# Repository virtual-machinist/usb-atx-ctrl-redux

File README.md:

# usb-atx-ctrl-redux

## Rationale

This project is a minified/reduced version of [usb-atx-ctrl](https://github.com/zappanaut/usb-atx-ctrl) project by Zappanaut.

The rationale behind this project is to have a standard PiKVM ATX breakout board installed in the case of the PC being controlled vs replacing it with a custom PCB like done in the aforementioned project.

## Design Choices and Components Used

1. RP2040-Zero (`RZ1`) is not soldered to the PCB directly, but using SMD female pin headers. If needed `RZ1` can be soldered through a set of male pin headers. This might however require offsetting the USB-C socket in the case model.  
2. `SW1` and `SW2` are 4.5x4.5x5mm 90° through-hole miniature tactile push-button switches with distance between the shield and switch terminals is ~2.0mm.

## Assembly

Assembly starts with SMD components, typically resistors, then LEDs, then optorelays. After that RP2040-Zero, tactile switches, then 8P8C socket.  

After PCB assembly it's recommended to print and use a [case](case/README.md) to protect the PCB from accidental damage and electrical shorts.

Assembled photos can be seen under [pictures](pictures/README.md).

## Usage

Setting up the RP2040-Zero is the same as in [usb-atx-ctrl](https://github.com/zappanaut/usb-atx-ctrl) project. The project requires a PC with an [ATX breakout board](https://github.com/pikvm/pikvm/blob/master/docs/atx_board.md) from the PiKVM project or some other solution that exposes a [compatible](https://github.com/pikvm/pikvm/blob/master/docs/atx_board/rj45.jpg) RJ-45 connector. 

## License

The project uses MIT license, except for the case which is [licensed](case/LICENSE) under Creative Commons Attribution 4.0 license ("CC-BY").

## Credits

1. [usb-atx-ctrl](https://github.com/zappanaut/usb-atx-ctrl) project by Zappanaut for most of the schematics and some of the symbols.

2. [Wright-Train-Works](https://github.com/acwright/Wright-Train-Works) project by Aaron Wright for the Amphenol connector STEP file.

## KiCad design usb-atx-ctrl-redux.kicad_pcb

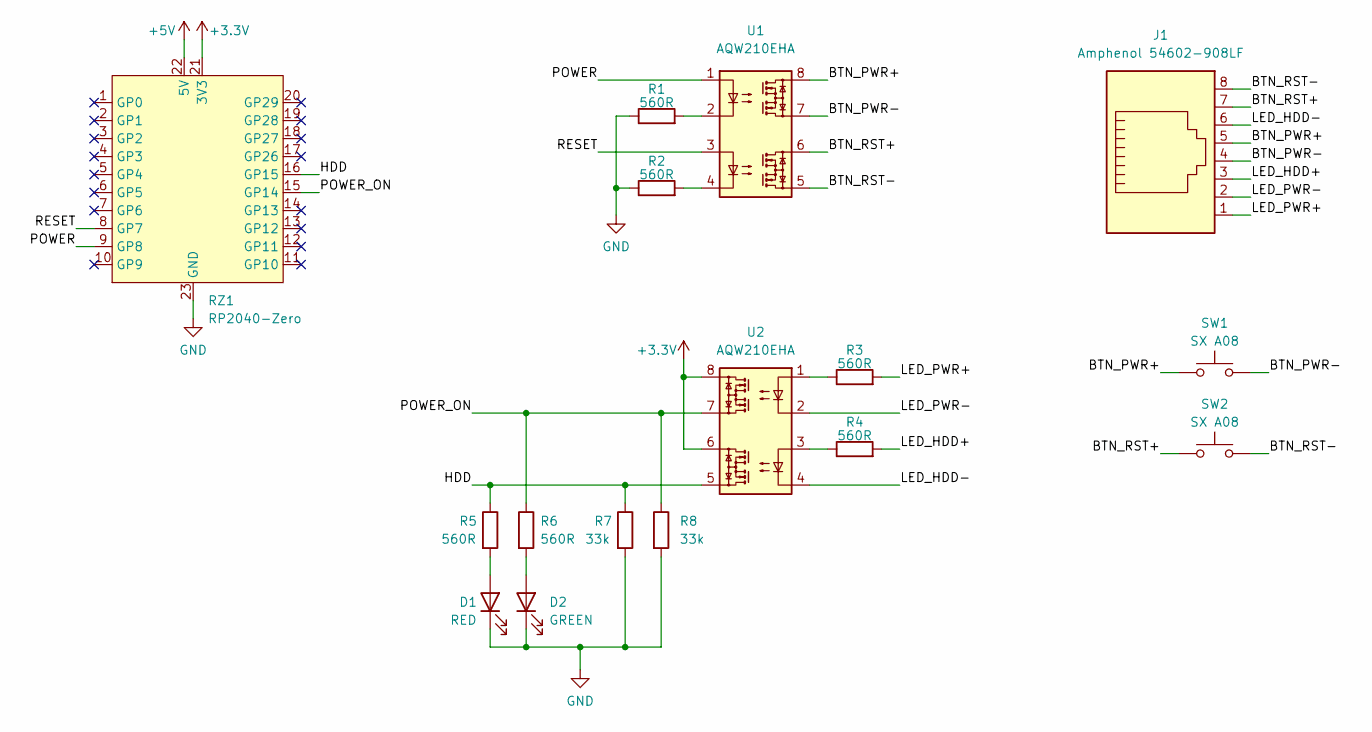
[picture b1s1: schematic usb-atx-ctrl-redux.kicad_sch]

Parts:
D1: RED; LED_0805_2012Metric_Pad1.15x1.40mm_HandSolder
D2: GREEN; LED_0805_2012Metric_Pad1.15x1.40mm_HandSolder
J1: Amphenol 54602-908LF; RJ45_Amphenol_54602-x08_Horizontal
R1, R2, R3, R4, R5, R6: 560R; R_0603_1608Metric_Pad0.98x0.95mm_HandSolder
R7, R8: 33k; R_0603_1608Metric_Pad0.98x0.95mm_HandSolder
RZ1: RP2040-Zero; RP2040-Zero_SMD
SW1, SW2: SX A08; Button_Switch_SX_A08
U1, U2: AQW210EHA; SMDIP-8_W7.62mm

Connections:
+3.3V: RZ1.21 (3V3), U2.6, U2.8
+5V: RZ1.22 (5V)
/BTN_PWR+: J1.5, SW1.1, U1.8
/BTN_PWR-: J1.4, SW1.2, U1.7
/BTN_RST+: J1.7, SW2.1, U1.6
/BTN_RST-: J1.8, SW2.2, U1.5
/HDD: R5.1, R7.1, RZ1.16 (GP15), U2.5
/LED_HDD+: J1.3, R4.2
/LED_HDD-: J1.6, U2.4
/LED_PWR+: J1.1, R3.2
/LED_PWR-: J1.2, U2.2
/POWER: RZ1.9 (GP8), U1.1
/POWER_ON: R6.1, R8.1, RZ1.15 (GP14), U2.7
/RESET: RZ1.8 (GP7), U1.3
GND: D1.1 (K), D2.1 (K), R1.1, R2.1, R7.2, R8.2, RZ1.23 (GND)
unnamed: D1.2 (A), R5.2
unnamed: D2.2 (A), R6.2
unnamed: R1.2, U1.2
unnamed: R2.2, U1.4
unnamed: R3.1, U2.1
unnamed: R4.1, U2.3

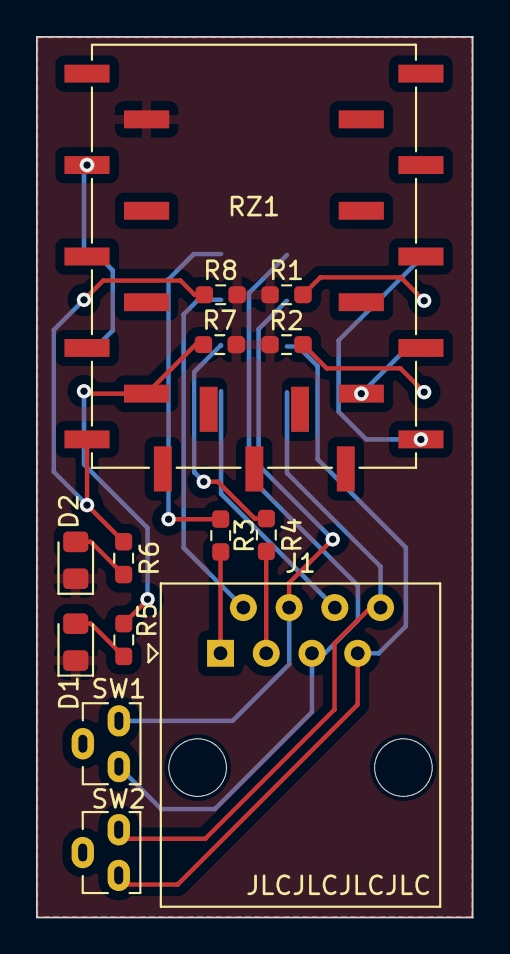
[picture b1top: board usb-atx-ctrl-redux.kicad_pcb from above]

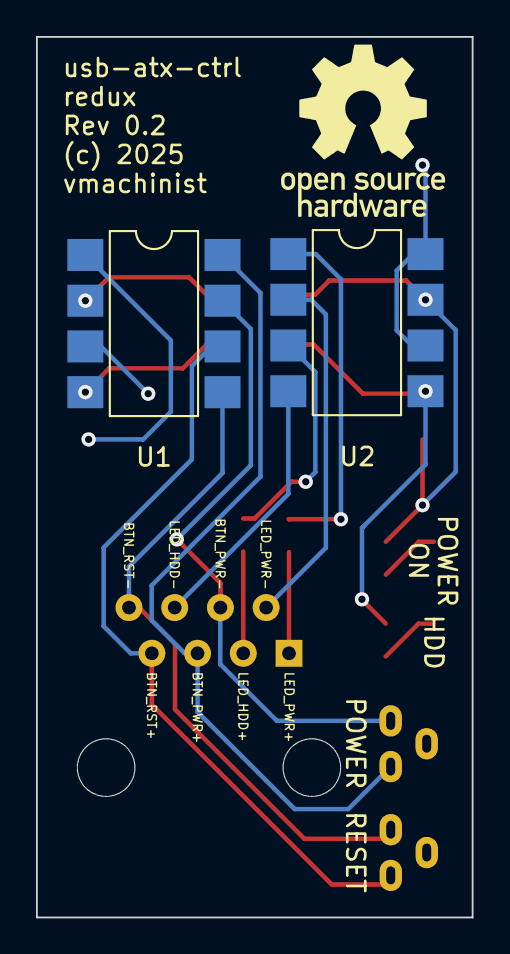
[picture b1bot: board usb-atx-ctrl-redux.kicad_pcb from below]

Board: 2 copper layers, 24.2 x 48.9 mm, 16 parts (2 on the bottom side), 20 nets.

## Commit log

2026-01-03 Gerber files
2026-01-03 KiCad project
2026-01-03 Add labels
2026-01-03 Fix GPIO assignment, 8P8C footprint, bump to KiCad 8
2026-01-03 Case project
2026-01-03 Move KiCad project to a subdirectory
2026-01-03 Add README and pictures

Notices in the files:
usb-atx-ctrl-redux.kicad_pcb:
(c) 2025
